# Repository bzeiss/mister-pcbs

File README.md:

# mister-pcbs

This site contains some stuff I have built for the excellent Mister project. You can more about the Mister project here: https://github.com/MiSTer-devel/Main_MiSTer/wiki

I tinker with electronics, release stuff when I feel like it and I make it public when it's maybe not perfect. I'm not an electronics expert, so I may not always know what I'm doing. I learn the necessary electronics as I use it. Use at your own risk.

Be smart. Don't just trust the stuff I offer for download here. Take a look at the schematic and the PCB design beforehand. 

Feedback is always very welcome :smile: Feel free to ask question in the [discussions](https://github.com/bzeiss/mister-pcbs/discussions).

***

The main content of this site (descriptions, documentations) can be found **[in the Wiki](https://github.com/bzeiss/mister-pcbs/wiki)**.

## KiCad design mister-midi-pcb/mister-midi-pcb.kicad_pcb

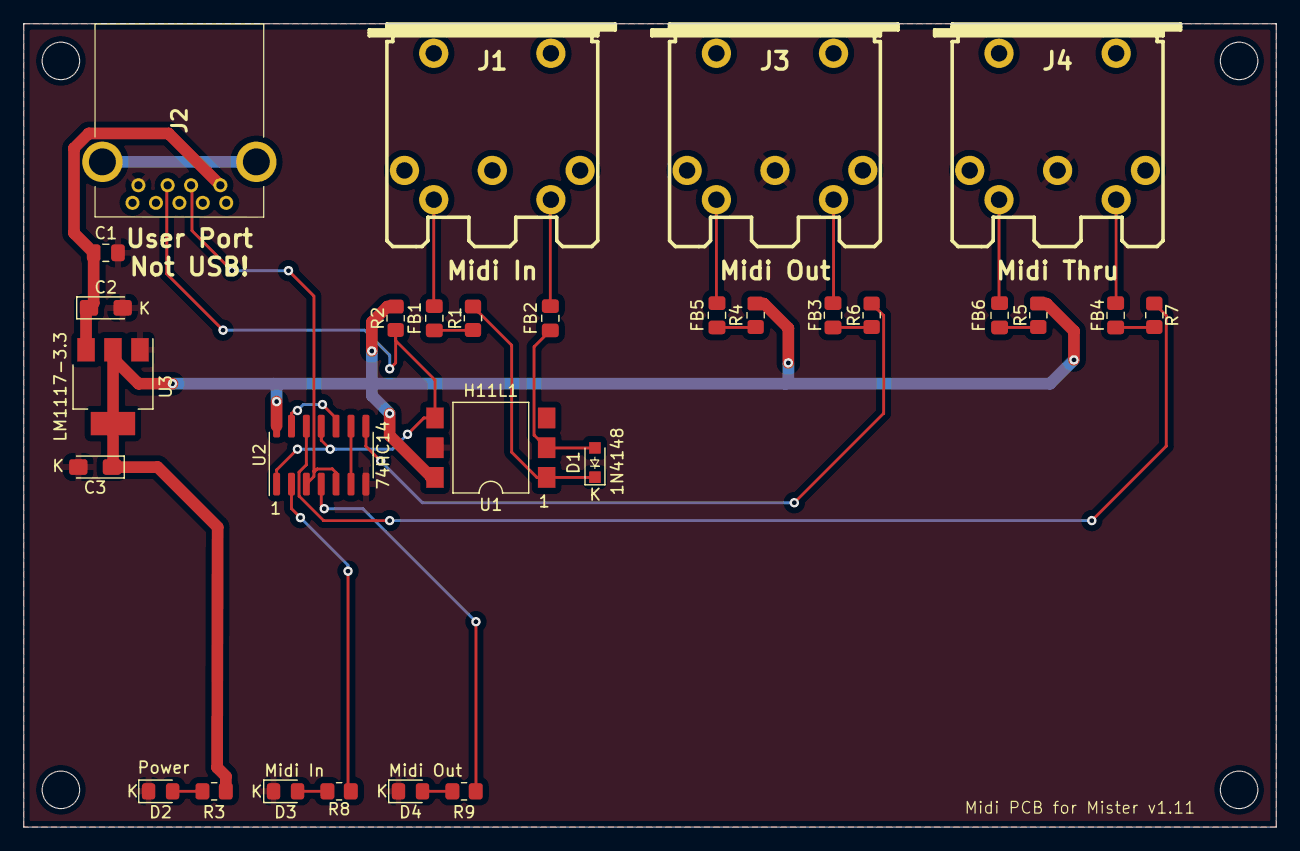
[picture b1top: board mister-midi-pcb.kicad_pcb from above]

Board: 2 copper layers, 106.9 x 68.6 mm, 29 parts (0 on the bottom side), 27 nets.

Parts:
C1: 100nF; C_0805_2012Metric_Pad1.18x1.45mm_HandSolder
C2, C3: 10uF; CP_EIA-3216-18_Kemet-A_Pad1.58x1.35mm_HandSolder
D1: 1N4148; D_SOD-323_HandSoldering
D2: Green LED; LED_0805_2012Metric_Pad1.15x1.40mm_HandSolder
D3: Blue LED; LED_0805_2012Metric_Pad1.15x1.40mm_HandSolder
D4: Yellow LED; LED_0805_2012Metric_Pad1.15x1.40mm_HandSolder
FB1, FB2, FB3, FB4, FB5, FB6: Ferrite_Bead; C_0805_2012Metric_Pad1.18x1.45mm_HandSolder
J1: Midi In; din-5
J2: USB3_A; GSB3111113HR
J3: Midi Out; din-5
J4: Midi Thru; din-5
R1: 220; R_0805_2012Metric_Pad1.20x1.40mm_HandSolder
R2: 470; R_0805_2012Metric_Pad1.20x1.40mm_HandSolder
R3, R8, R9: 2k; R_0805_2012Metric_Pad1.20x1.40mm_HandSolder
R4, R5: 33; R_0805_2012Metric_Pad1.20x1.40mm_HandSolder
R6, R7: 10; R_0805_2012Metric_Pad1.20x1.40mm_HandSolder
U1: H11L1; SMDIP-6_W9.53mm_Clearance8mm
U2: 74HC14; SO-14_3.9x8.65mm_P1.27mm
U3: LM1117-3.3; SOT-223-3_TabPin2

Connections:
+3V3: C3.1, R2.1, R3.2, R4.2, R5.2, U1.6, U2.14 (VCC), U3.2 (VO)
+5V: C1.1, C2.1, J2.1 (VBUS), U3.3 (VI)
GND: C1.2, C2.2, C3.2, D2.1 (K), D3.1 (K), D4.1 (K), J2.4 (GND), J3.2, J4.2, U1.5, U2.7 (GND), U3.1 (GND)
Midi_In_RX: J2.3 (D+), R2.2, U1.4, U2.1, U2.11
Midi_In_RX_Inv: R8.2, U2.2
Midi_Out_TX: J2.2 (D-), U2.3, U2.5
Midi_Out_TX_INV: R9.2, U2.4
unnamed: D1.1 (K), R1.1, U1.1
unnamed: D1.2 (A), FB2.1, U1.2
unnamed: D2.2 (A), R3.1
unnamed: D3.2 (A), R8.1
unnamed: D4.2 (A), R9.1
unnamed: FB1.1, R1.2
unnamed: FB1.2, J1.4
unnamed: FB2.2, J1.5
unnamed: FB3.1, J3.5
unnamed: FB3.2, R6.2
unnamed: FB4.1, J4.5
unnamed: FB4.2, R7.1
unnamed: FB5.1, R4.1
unnamed: FB5.2, J3.4
unnamed: FB6.1, R5.1
unnamed: FB6.2, J4.4
unnamed: R6.1, U2.8
unnamed: R7.2, U2.12
unnamed: U2.6, U2.9
unnamed: U2.10, U2.13

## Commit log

2021-06-22 reworked pcb with 3.3v
2021-06-22 small fix.
2021-06-22 gerber files
2021-06-24 out and thru go through buffer now.
2021-06-24 updated gerber.
2021-06-26 small trace improvements.
2021-06-26 added capacitors for ldo
2021-06-27 updated gerbers, holes were missing.
2021-07-09 Fix #2,#3
2021-07-12 v1.1 of the midi pcb. fixed a couple of problems from the first prototype board.
2021-09-06 added bom
2022-03-30 kicad 6 migration, jlcpcb assembly files.
2022-04-08 updated pdfs
